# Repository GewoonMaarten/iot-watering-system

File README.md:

# IOT watering system 
Watering system with moisture sensor and firebase database.

## Firebase 
This project uses Firebase from Google to store the data collected from the moisture sensor. The Arduino code only uploads the value from the moisture sensor and whether the pump is on to the database. There is a Nodejs project include which, when uploaded as a cloud function to the Firebase database will add a datetime to the newly added values. Another function is added to clean the measurements that are older than one month. This data is not valuable to me so remove it.

### The JSON structure
The cloud function will format a datetime based on the machine time. the format is a YYYY-MM-DD HH:mm:ss, e.g.: `2017-04-13 16:59:23`.
The Arduino codes add a boolean based on whether the pump is currently active. And the value the value of the moisture sensor is added.
This all combined gives the following data structure: 
``` JSON
{
  "measurement" : {
    "-KgQiGUIjxPrxezXVW1H" : {
      "dateTime" : "2017-04-13 16:59:23",
      "isWatering" : 0,
      "value" : 2.72
    }
  }
} 
```

## The Hardware
### Parts list:
I bought most of the things on Ali Express so thats where I will provide links for.
* [WEmos D1 mini](https://www.aliexpress.com/item/D1-mini-V2-Mini-NodeMcu-4M-bytes-Lua-WIFI-Internet-of-Things-development-board-based-ESP8266/32529101036.html?spm=2114.13010608.0.0.lmmSkm)
* [Power Relay (5v)](https://www.aliexpress.com/item/10PCS-RELAY-5V-SRD-5VDC-SL-C-T73-5V-Power-Relay-NEW/32444246523.html?spm=2114.13010608.0.0.lmmSkm)
* [Small pump](https://www.aliexpress.com/item/1Pcs-DC-12v-D2-Small-Dosing-Pump-2mm-DIY-Peristaltic-Tube-Head-For-Aquarium-Lab-Chemical/32650282709.html?spm=2114.13010608.0.0.lmmSkm)
* [Tube](https://www.aliexpress.com/item/3M-2-4mm-2x4mm-Creamy-White-Black-Red-Yellow-Medical-Food-Grade-Drink-Machine-Flexible-Pipe/32787873264.html?spm=2114.13010608.0.0.lmmSkm)
* [Moisture sensor](https://www.aliexpress.com/item/1Pcs-Soil-Hygrometer-Detection-Module-Soil-Moisture-Sensor/2035877568.html?spm=2114.13010608.0.0.lmmSkm)
* A way to convert 12v to 5v. Is used [this](https://www.aliexpress.com/item/8pcs-10W-Breadboard-Power-Module-DC-6-5V-23V-12V-to-5V-DC-DC-Converter-replace/32326359914.html?spm=2114.13010608.0.0.lmmSkm). But you could use a 5v regulator.
* Diode
* NPN transistor. I used a BC547
* Wire
* 12v powersupply with 5.5 * 2.1mm DC jack

#### Schematic:

#### PCB:

The final product: <br />

#### Related
How to plot the sensor data:
[Systems.maartens.website](http://maartens.website/)

License: [MIT](https://github.com/GewoonMaarten/iot-watering-system/blob/master/LICENSE)

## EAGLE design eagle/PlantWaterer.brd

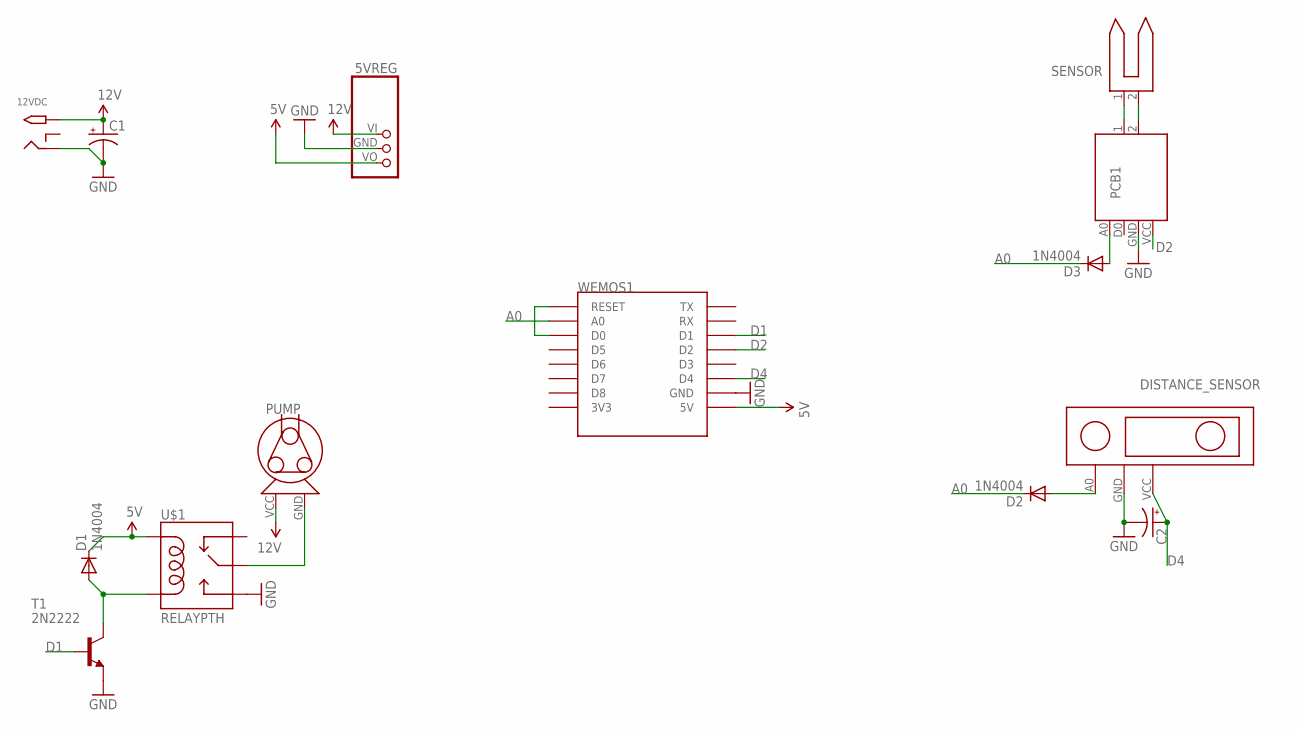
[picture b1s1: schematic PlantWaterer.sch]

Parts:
5VREG: 5V_REG
12VDC: 2.1MMJACK; PJ-102A
C1: 100UF-25V-20%(PTH); CPOL-RADIAL-100UF-25V
C2: 10UF-25V-20%(PTH); CPOL-RADIAL-10UF-25V
D1, D2, D3: 1N4004; DO41-10
DISTANCE_SENSOR: SHARP_GP2Y0A21YK
PCB1: WATER_SENSOR_PCB
PUMP: PERISTALTIC_PUMP
SENSOR: WATER_SENSOR
T1: 2N2222; TO92-EBC-OVAL
U$1: RELAYPTH; SRD-05VDC-SL-C
WEMOS1: WEMOS-D1-MINI

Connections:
5V: 5VREG.VO, D1.C, U$1.COIL1, WEMOS1.5V
12V: 5VREG.VI, 12VDC.TIP, C1.1 (+), PUMP.VCC
A0: D2.C, D3.C, WEMOS1.A0
D1: T1.B, WEMOS1.D1
D2: PCB1.VCC, WEMOS1.D2
D4: C2.1 (+), DISTANCE_SENSOR.VCC, WEMOS1.D4
GND: 5VREG.GND, 12VDC.RING, C1.2 (-), C2.2 (-), DISTANCE_SENSOR.GND, PCB1.GND, T1.E, U$1.SWOPEN, WEMOS1.GND
unnamed: D1.A, T1.C, U$1.COIL0
unnamed: D2.A, DISTANCE_SENSOR.A0
unnamed: WEMOS1.D0, WEMOS1.RESET
unnamed: PUMP.GND, U$1.SWCOMMON
unnamed: PCB1.1, SENSOR.1
unnamed: PCB1.2, SENSOR.2
unnamed: D3.A, PCB1.A0

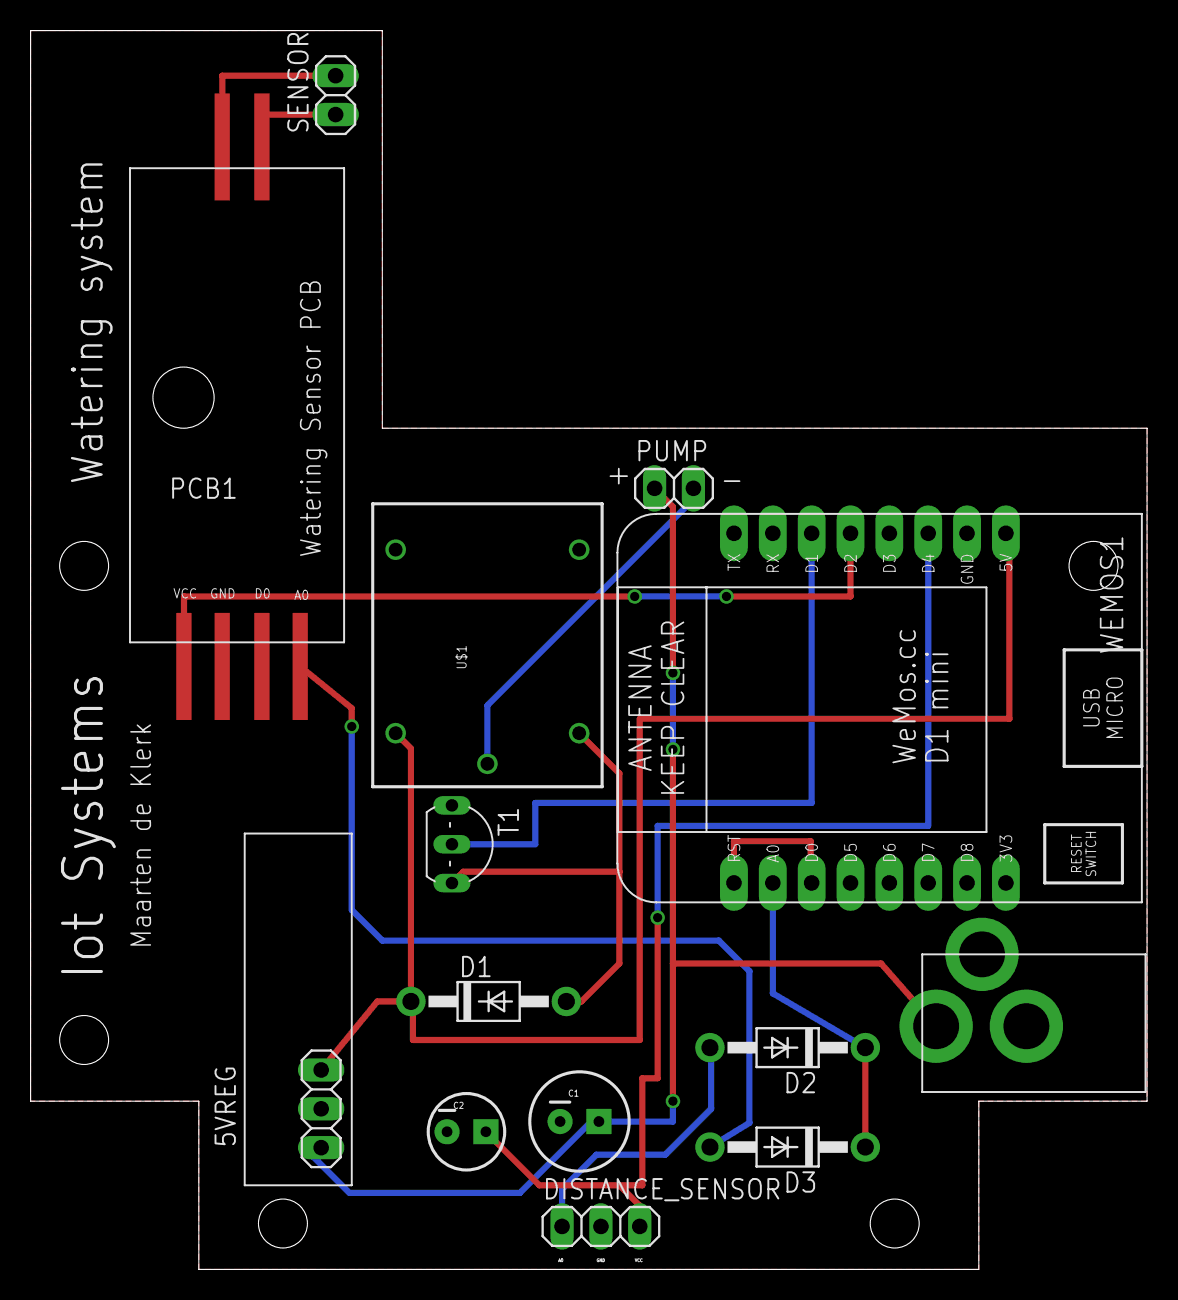
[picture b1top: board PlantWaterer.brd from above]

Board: 2 copper layers, 73.0 x 81.0 mm, 14 parts (0 on the bottom side), 14 nets.

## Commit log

2017-03-29 added firebase cloud function
2017-03-29 added 'addDateTime' cloud function for firebase
2017-03-29 fixed dateformat issue
2017-03-29 finished watering code
2017-03-30 Updated schematic
2017-04-03 Updated schematics
2017-04-07 Picutre of final board
2017-04-08 Updated datetime format
2017-04-13 Change datetime and added database cleanup function
2017-04-13 Fixed issue where functions are executed twice
2017-04-13 Added image, fixed typo and fixed schematic
2017-04-14 Small changes
2017-04-15 Database migration and Added ability to update over wifi
2017-07-13 Added pcb layout

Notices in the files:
parts and their libraries:
SparkFun-Capacitors: Licensing: Creative Commons ShareAlike 4.0 International - https://creativecommons.org/licenses/by-sa/4.0
